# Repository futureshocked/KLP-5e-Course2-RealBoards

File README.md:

# KLP 5e — Course 2: Real Boards — project files

Companion project files for *KiCad Like a Pro, 5th Edition*, Course 2 ("Real boards"). Each
hands-on project is captured as a series of numbered stages, one per build step in the course,
so you can start from any point or check your own work against a known-good result.

Clone this repository, or download the stage folder you need, and carry on from there. Modules 1
and 2 work in the symbol and footprint editors with no project open, so their stages are library
folders; from Module 3 on, every stage is a complete KiCad project that opens on its own.

## About the course and the book series

To learn more about Course 2 and the *KiCad Like a Pro, 5th Edition* book series, visit the
[KLP 5e course page](https://techexplorations.com/kicad/course/).

## Projects

| Folder | Project | Used in |
|---|---|---|
| [`klp5e-c2-m1-drv8833-parts/`](klp5e-c2-m1-drv8833-parts/) | The DRV8833 symbol and footprint, authored from the datasheet, with Activities A1.1 and A2.1 | Modules 1 and 2 |
| [`klp5e-c2-m3-standin-board/`](klp5e-c2-m3-standin-board/) | The DRV8833 stand-in board, set up with net classes, sizes, custom rules and severities, with Activity A3.1; then routed and given its copper zones | Modules 3 and 4 |
| [`klp5e-c2-m5-led-matrix/`](klp5e-c2-m5-led-matrix/) | The four-cell MAX7219 LED matrix: one cell built, stamped four times and copied with Repeat Layout, with Activity A5.1 | Module 5 |
| [`klp5e-c2-m6-drv8833/`](klp5e-c2-m6-drv8833/) | The DRV8833 two-motor driver board, the capstone: sheet, board setup, driver stage placed first, routed, poured and finished with its silkscreen, with Activity A6.1; checked, plotted and ordered; then the recipes for its next revision; the bonus set 8U's sourcing fields and bills | Modules 6, 8U (bonus set), 9 and 11 |
| [`klp5e-c2-m7-drv8833-4motor/`](klp5e-c2-m7-drv8833-4motor/) | The capstone extended to four motors: the driver stage captured as a design block and placed a second time, with Activity A7.1; its sourcing fields, build variants and bills; plotted, with Activity A9.1 | Modules 7, 8 and 9 |
| [`module-10-assembly-handouts/`](module-10-assembly-handouts/) | The printable bench sheets for assembling the two-motor board with a stencil and hotplate, and by hand | Module 10 |

Each activity folder also holds the activity's slide deck, `slides.html`. Download it and open it in
a browser (press `F` for fullscreen, arrow keys to move), so you can keep the task on screen
instead of pausing the video.

More projects are added as each module is recorded. See each project's own README for what each
stage contains.

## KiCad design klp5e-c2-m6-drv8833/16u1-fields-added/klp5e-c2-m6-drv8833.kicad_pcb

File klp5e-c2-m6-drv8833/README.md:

# klp5e-c2-m6-drv8833 stages

One folder per step of Module 6's capstone: a two-motor driver board built round the DRV8833,
using the symbol and footprint you authored in Modules 1 and 2. The module draws the sheet, sets
the board up, places the driver stage first, routes the board and writes the rule that covers the chip's breakout,
pours the ground, labels the silkscreen and finishes it with the title block and logos. Each stage
is the project as it stood at the end of a lecture or bonus video and the start of the next one.

**Every stage is a complete KiCad project.** Open the `.kicad_pro` in a stage folder and it loads
on its own: the schematic, the board, the project's symbol and footprint library tables,
`Libraries/` (the DRV8833 symbol and footprint) and `datasheets/`. From `05-board-setup` on, the
stage also holds the `.kicad_dru` custom rules. Each stage also holds `tools/checknet.py`, the
netlist checker, and `tools/checkplacement.py`, the placement checker. Copy a stage folder out of
the repository before you work in it, and do not open two stages at once.

| Stage | State | Produced by |
|---|---|---|
| `00-start` | An empty A4 sheet with the title block, an empty board, the `Default` net class only, the DRV8833 library and datasheet, and the two checkers | bonus B6.1 |
| `01-classes-and-stage` | The `Power` and `Sense` net classes and their four patterns; the eight-part driver stage placed on the sheet, unannotated and unwired | lecture 6.4 |
| `02-sheet-placed` | Every part placed and annotated, with values and footprints filled in; still no wire | bonus B6.2 |
| `03-wired` | The sheet wired and labelled; ERC reports two `power_pin_not_driven` errors | lecture 6.5 |
| `04-netlist-clean` | Two `PWR_FLAG`s added; ERC clean; checknet's three checks pass | lecture 6.6 |
| `05-board-setup` | The fabricator's limits and mask clearance imported, default severities, two copper layers, the two-rule `.kicad_dru`; the board is still empty | lecture 6.7 |
| `06-outline` | Predefined track and via sizes, silkscreen default 0.15 mm, the 20 footprints on the board, the outline drawn | bonus B6.3 |
| `07-stage-placed` | The eight driver-stage parts placed; the other twelve still off the board | lecture 6.8 |
| `08-all-placed` | Every part at its table position, the driver stage locked; the board agrees with the sheet | bonus B6.4 |
| `09-bridge-a` | `VM_IN`, `VM`, `AOUT1`, `AOUT2` and `AISEN` routed on `F.Cu`. The start of A6.1 | lecture 6.9 |
| `10-bridge-b` | `J3` re-pinned and bridge B routed: `BOUT1`, `BOUT2` and `BISEN`. The worked solution to A6.1 | bonus B6.5 |
| `11-logic-routed` | The logic nets routed; only `GND` is left unconnected | bonus B6.6 |
| `12-breakout-area` | The rule area `U1_breakout` drawn round the chip, with a deliberate what-if: two narrow pieces on `AOUT1` and `BOUT1` that the DRC flags while the rule still follows the courtyard | lecture 6.10 |
| `13-rule-on-area` | The breakout rule aimed at the rule area; the DRC is clear | lecture 6.11 |
| `14-ground-poured` | The `GND` pour on both layers, with ties to the back for the ground pads in pockets of front copper. One tie via is still at the default size | lecture 6.12 |
| `15-labelled` | The designators and the connector legends on the silkscreen | lecture 6.13 |
| `16-finished` | The title block and the KiCad and Tech Explorations logos; the DRC reports no violation and parity is clean. The finished board, the start of Module 9 and of the bonus set 8U | bonus B6.7 |
| `16u1-fields-added` | The four sourcing field templates in the project; `U1`'s supplier fields corrected; `J1` to `J3`, `R2` and `R3` filled | bonus set, lecture 8.2U |
| `16u2-fields-filled` | `MPN`, `Manufacturer` and `Supplier` filled on all 13 lines of the bill | bonus set, B8.1U |
| `16u3-without-sense` | The design variant `without-sense`, with its overrides on `R2` and `R3` | bonus set, lecture 8.3U |
| `16u4-bills-exported` | The bill's export file set to `BOM/bom_${VARIANT}.csv`; `BOM/` holds one bill for each build | bonus set, lecture 8.5U |
| `16u5-assembly-bill` | The assembler's template columns and BOM names saved in the project; `BOM/` also holds the bill shaped to the template | bonus set, lecture 8.6U |
| `17-dfm-checked` | The same board after the DRC with the fab's numbers and the HQ DFM plugin; neither needed a fix | lecture 9.2 |
| `18-finish-enig` | The surface finish set to ENIG in Board Setup; nothing else changed | lecture 9.3 |
| `19-plotted` | The plot settings saved; `Gerber/` holds the nine Gerbers, the drill file and its map, the job file, the position file and `klp5e-c2-m6-drv8833-fab.zip`, the archive sent to the factory | lecture 9.4 |
| `20-fab-checked` | The same files after the three checks on the plotted files; nothing needed a fix. This is the board that was ordered and that Module 10 assembles, and the start of Module 11 | lecture 9.5 |
| `21-control-bus` | The four control lines drawn as the bus `CTRL{AIN1 AIN2 BIN1 BIN2}`; the board's control nets are now `/CTRL.AIN1` to `/CTRL.BIN2` | lecture 11.2 |
| `22-logic-table` | The DRV8833's H-bridge logic table on the back silkscreen | lecture 11.3 |
| `23-qr-code` | A QR code for `techexplorations.com/kicad`, made with the footprint wizard and saved as `te_qr_code` in `peters_custom_Library`, on the back silkscreen | lecture 11.4 |
| `24-teardrops` | Teardrops on the board's pads and vias; pours refilled | lecture 11.5 |

Stage `16-finished` adds a second project library, `Logo` (`Libraries/Logo.pretty`), holding the Tech
Explorations logo footprints. Its row is in the stage's `fp-lib-table`.

Stages `16u1` to `16u5` belong to the bonus set 8U, *The BOM and a second build*. It teaches
Module 8's skills again on this two-motor board: the sourcing fields, the `without-sense` build and
the bills. The stages branch off `16-finished`, and Module 9 does not continue from them.
`17-dfm-checked` follows `16-finished`, not `16u5-assembly-bill`, so the stages from `17` on have
no sourcing fields and no variants. Module 8 itself works on the four-motor board in
[`klp5e-c2-m7-drv8833-4motor/`](../klp5e-c2-m7-drv8833-4motor/).

Stages `17` to `20` are the board as it was checked and ordered in Module 9. Stages `21` to `24`
are the recipes of Module 11: touches for the board's next revision, so they hold no plotted files
and nothing in them was ordered.

## Checking the netlist (lecture 6.6)

From a stage folder, from `03-wired` on:

```bash
kicad-cli sch export netlist -o net.net klp5e-c2-m6-drv8833.kicad_sch
python3 tools/checknet.py net.net --nets
python3 tools/checknet.py net.net --u1-pins
python3 tools/checknet.py net.net --classes
```

On `04-netlist-clean` and later, all three pass.

## Checking the placement (bonus B6.4)

From a stage folder, from `08-all-placed` on:

```bash
python3 tools/checkplacement.py --outline --fit --overlap --proximity
```

On `07-stage-placed` it fails, because twelve parts are still off the board.

## Activity A6.1

[`A6.1-activity/`](A6.1-activity/) has everything for the activity in its own README: where you
start, the task, the settings, the acceptance list and what to do if you get stuck. The folder also
holds a record sheet (`record-sheet.md`) and the lecture's slide deck (`slides.html`). Start from
`09-bridge-a`. The worked solution is bonus B6.5, and its stage is `10-bridge-b`.

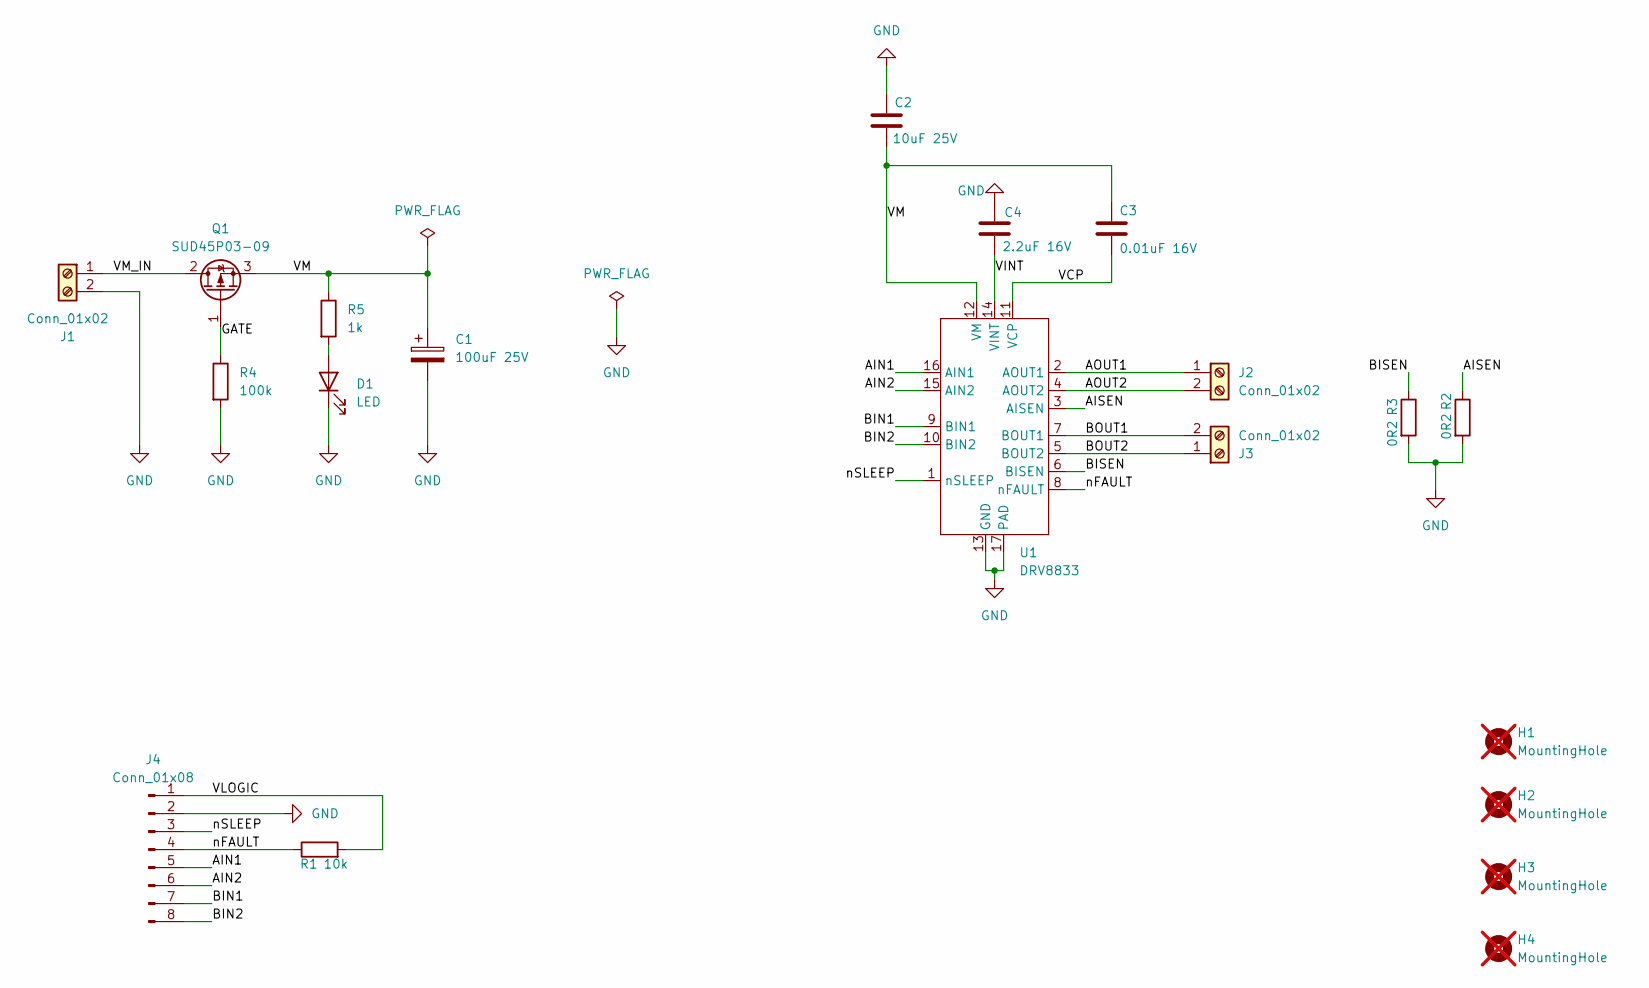
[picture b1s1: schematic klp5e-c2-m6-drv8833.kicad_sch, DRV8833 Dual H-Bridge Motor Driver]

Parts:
C1: 100uF 25V; CP_Radial_D6.3mm_P2.50mm
C2: 10uF 25V; C_0805_2012Metric
C3: 0.01uF 16V; C_0603_1608Metric
C4: 2.2uF 16V; C_0603_1608Metric
D1: LED; LED_0805_2012Metric
H1, H2, H3, H4: MountingHole; MountingHole_3.2mm_M3; not fitted
J1, J2, J3: Conn_01x02; TerminalBlock_Phoenix_MKDS-1,5-2-5.08_1x02_P5.08mm_Horizont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; MPN 1715721
J4: Conn_01x08; PinHeader_1x08_P2.54mm_Vertical
Q1: SUD45P03-09; TO-252-2
R1: 10k; R_0603_1608Metric
R2, R3: 0R2; R_1206_3216Metric; MPN CSR1206FKR200
R4: 100k; R_0603_1608Metric
R5: 1k; R_0603_1608Metric
U1: DRV8833; HTSSOP-16-1EP_DRV8833_PD; MPN DRV8833PWPR

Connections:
/AIN1: J4.5, U1.16 (AIN1)
/AIN2: J4.6, U1.15 (AIN2)
/AISEN: R2.1, U1.3 (AISEN)
/AOUT1: J2.1, U1.2 (AOUT1)
/AOUT2: J2.2, U1.4 (AOUT2)
/BIN1: J4.7, U1.9 (BIN1)
/BIN2: J4.8, U1.10 (BIN2)
/BISEN: R3.1, U1.6 (BISEN)
/BOUT1: J3.2, U1.7 (BOUT1)
/BOUT2: J3.1, U1.5 (BOUT2)
/GATE: Q1.1 (G), R4.1
/VCP: C3.2, U1.11 (VCP)
/VINT: C4.2, U1.14 (VINT)
/VLOGIC: J4.1, R1.2
/VM: C1.1, C2.2, C3.1, Q1.3 (S), R5.1, U1.12 (VM)
/VM_IN: J1.1, Q1.2 (D)
/nFAULT: J4.4, R1.1, U1.8 (nFAULT)
/nSLEEP: J4.3, U1.1 (nSLEEP)
GND: C1.2, C2.1, C4.1, D1.1 (K), J1.2, J4.2, R2.2, R3.2, R4.2, U1.13 (GND), U1.17 (PAD)
unnamed: D1.2 (A), R5.2

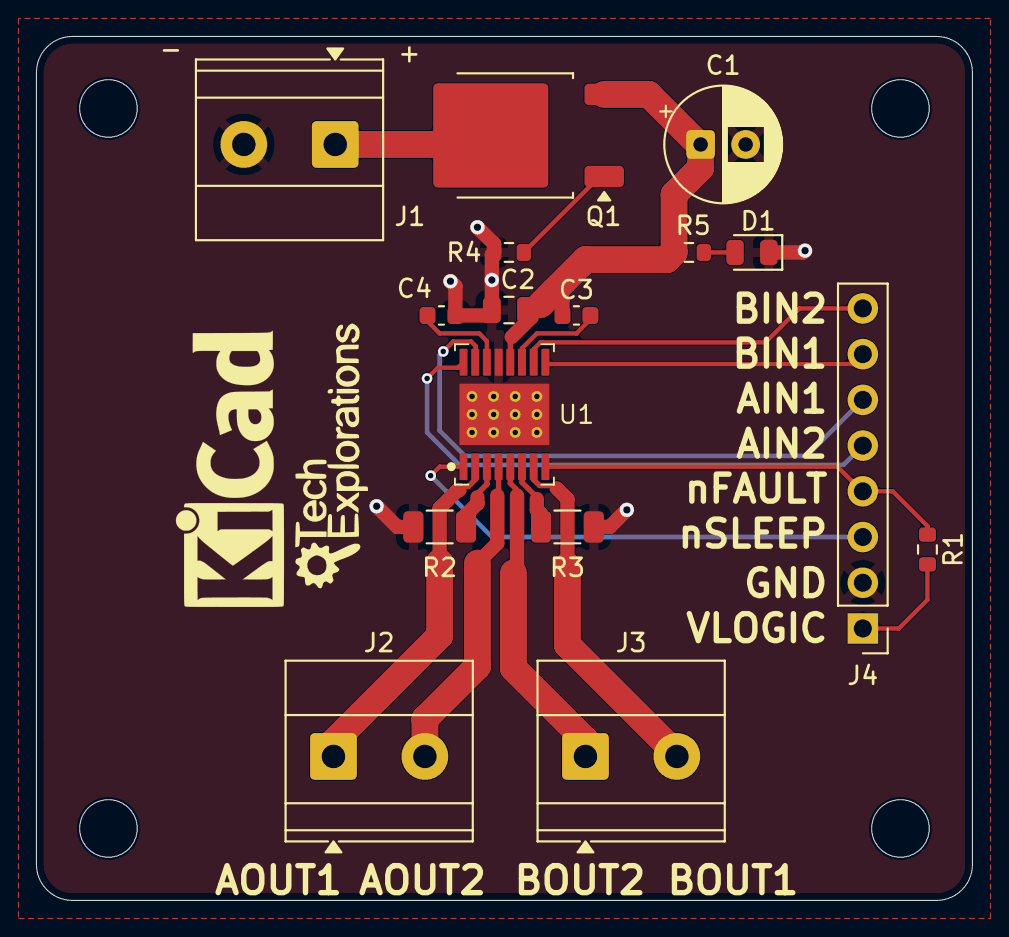
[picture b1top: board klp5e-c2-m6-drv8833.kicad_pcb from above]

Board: 2 copper layers, 52.0 x 48.0 mm, 20 parts (0 on the bottom side), 20 nets.

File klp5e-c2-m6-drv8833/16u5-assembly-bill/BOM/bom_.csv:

"Reference","Value","Footprint","Qty","DNP","SupplierURL","MPN","Manufacturer","Supplier"
"C1","100uF 25V","Capacitor_THT:CP_Radial_D6.3mm_P2.50mm","1","","","EEU-FR1E101","Panasonic","Farnell UK"
"C2","10uF 25V","Capacitor_SMD:C_0805_2012Metric","1","","","GRM21BR61E106KA73L","Murata","TTI Europe"
"C3","0.01uF 16V","Capacitor_SMD:C_0603_1608Metric","1","","","0603YC103JAT2A","KYOCERA AVX","Future Electronics EMEA"
"C4","2.2uF 16V","Capacitor_SMD:C_0603_1608Metric","1","","","EMK107BB7225KA-T","Taiyo Yuden","RS UK"
"D1","LED","LED_SMD:LED_0805_2012Metric","1","","","150080GS75000","Würth Elektronik","Farnell UK"
"J1,J2,J3","Conn_01x02","TerminalBlock_Phoenix:TerminalBlock_Phoenix_MKDS-1,5-2-5.08_1x02_P5.08mm_Horizontal","3","","","1715721","Phoenix Contact","Farnell UK"
"J4","Conn_01x08","Connector_PinHeader_2.54mm:PinHeader_1x08_P2.54mm_Vertical","1","","","61300811121","Würth Elektronik","DigiKey"
"Q1","SUD45P03-09","Package_TO_SOT_SMD:TO-252-2","1","","","SUD45P03-09-GE3","Vishay","Farnell UK"
"R1","10k","Resistor_SMD:R_0603_1608Metric","1","","","RC0603FR-0710KL","Yageo","RS UK"
"R2,R3","0R2","Resistor_SMD:R_1206_3216Metric","2","","","CSR1206FKR200","Stackpole Electronics","Future Electronics NA"
"R4","100k","Resistor_SMD:R_0603_1608Metric","1","","","RC0603FR-07100KL","Yageo","RS UK"
"R5","1k","Resistor_SMD:R_0603_1608Metric","1","","","RC0603FR-071KL","Yageo","Farnell UK"
"U1","DRV8833","peters_custom_Library:HTSSOP-16-1EP_DRV8833_PD","1","","https://uk.farnell.com/texas-instruments/drv8833pwpr/ic-moto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","DRV8833PWPR","Texas Instruments","Farnell UK"

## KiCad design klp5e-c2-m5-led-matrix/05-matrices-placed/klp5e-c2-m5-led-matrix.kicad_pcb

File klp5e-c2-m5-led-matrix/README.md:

# klp5e-c2-m5-led-matrix stages

One folder per step of Module 5's warm-up board: four MAX7219 cells, each driving an 8 × 8 LED
matrix, on a 100 × 50 mm board, fed by an Arduino Nano. The module builds one cell, stamps it four
times in the schematic, and routes it once on the board before copying it to the other three. Each
stage is the project as it stood at the end of a lecture and the start of the next one.

**Every stage is a complete KiCad project.** Open the `.kicad_pro` in a stage folder and it loads
on its own: the schematic, the board, the `.kicad_dru` custom rules, the project's symbol,
footprint and design block library tables, and `Libraries/`, which holds the matrix, the Nano and
the logo footprints, the symbols, the `MAX7219-Cell` design block and the 3D models. Each stage
also holds `tools/checknet.py`, the netlist checker used in lecture 5.5. Copy a stage folder out of
the repository before you work in it, and do not open two stages at once.

| Stage | State | Produced by |
|---|---|---|
| `00-start` | The once-only parts (the Nano, USB-C input, the MOSFET power switch, the buttons and their resistors), power symbols and labels; no cell yet; the board outline and the fabricator's limits; no footprints on the board | bonus B5.1 |
| `01-first-cell` | The `POWER` net class; cell 1 drawn and wired, `DIN` and `DOUT` bare | lecture 5.3 |
| `02-cell-footprints` | The cell's five footprints assigned | bonus B5.2 |
| `03-four-cells` | The cell saved as the `MAX7219-Cell` design block and placed three more times; the cascade links drawn, **with one mislabelled link**: the mistake lecture 5.5 finds | lecture 5.4 |
| `04-netlist-clean` | The link label fixed; ERC clean; all five checknet runs pass | lecture 5.5 |
| `05-matrices-placed` | Footprints on the board as four groups; matrices `DS1` to `DS4` at 20 mm pitch, locked | lecture 5.6 |
| `06-once-only-placed` | The once-only parts and the four mounting holes placed; cells 2 to 4 roughly under their matrices | bonus B5.3 |
| `07-reference-started` | Cell 1 routed on the back | lecture 5.7 |
| `08-reference-routed` | The same board as `07`: cell 1, the reference cell, fully routed | lecture 5.7 |
| `09-repeated` | Groups renamed `DS1` to `DS4`, each with a placement rule area; cells 2 to 4 placed and routed from cell 1 by Repeat Layout | lecture 5.8 |
| `10-shared-wiring` | The wiring the cells share (power, clock, load and the cascade) drawn into and out of cells 1 and 2. The start of A5.1 | bonus B5.5 |
| `11-copied` | Cells 3 and 4 given their shared wiring by one Repeat Layout from cell 2, unrepaired. A5.1's worked solution | bonus B5.6 |
| `12-repaired` | The two stacked vias the copy left at the cell 3 and cell 4 seams removed; no DRC warnings, only `GND` unconnected | lecture 5.9 |
| `13-first-pour` | One `GND` zone on both layers, filled: much of the back's copper is cut away between the cells' tracks | lecture 5.10 |
| `14-stitched` | `DIN1` and the cascade links re-routed; `GND` vias stitched through the pour until every filled piece reaches one; nothing unconnected | bonus B5.7 |
| `15-finished` | Reference designators resized, the silkscreen labels and the board's name and version added, the Nano's 3D model placed: the finished board | bonus B5.8 |

Up to `12-repaired`, every stage leaves `GND` unconnected: the copper pour joins it in lecture
5.10, and the stitching vias in `14-stitched` finish the job. When you open `13-first-pour` or a
later stage, press B to refill the pour before you read it or run the DRC.

## Checking the netlist (lecture 5.5)

From a stage folder, from `03-four-cells` on:

```bash
kicad-cli sch export netlist -o net.net klp5e-c2-m5-led-matrix.kicad_sch
for n in 1 2 3 4; do python3 tools/checknet.py net.net --cell $n; done
python3 tools/checknet.py net.net --cascade 4
```

On `03-four-cells` the cascade run fails at the mislabelled link; on `04-netlist-clean` all five
runs pass.

## Activity A5.1

[`A5.1-activity/`](A5.1-activity/) has everything for the activity in its own README: where you
start, the steps, the acceptance list and where you finish. The folder also holds a record sheet
(`record-sheet.md`) and the lecture's slide deck (`slides.html`). Start from `10-shared-wiring`,
and compare your result with `11-copied` only after you have checked every line of the acceptance
list.

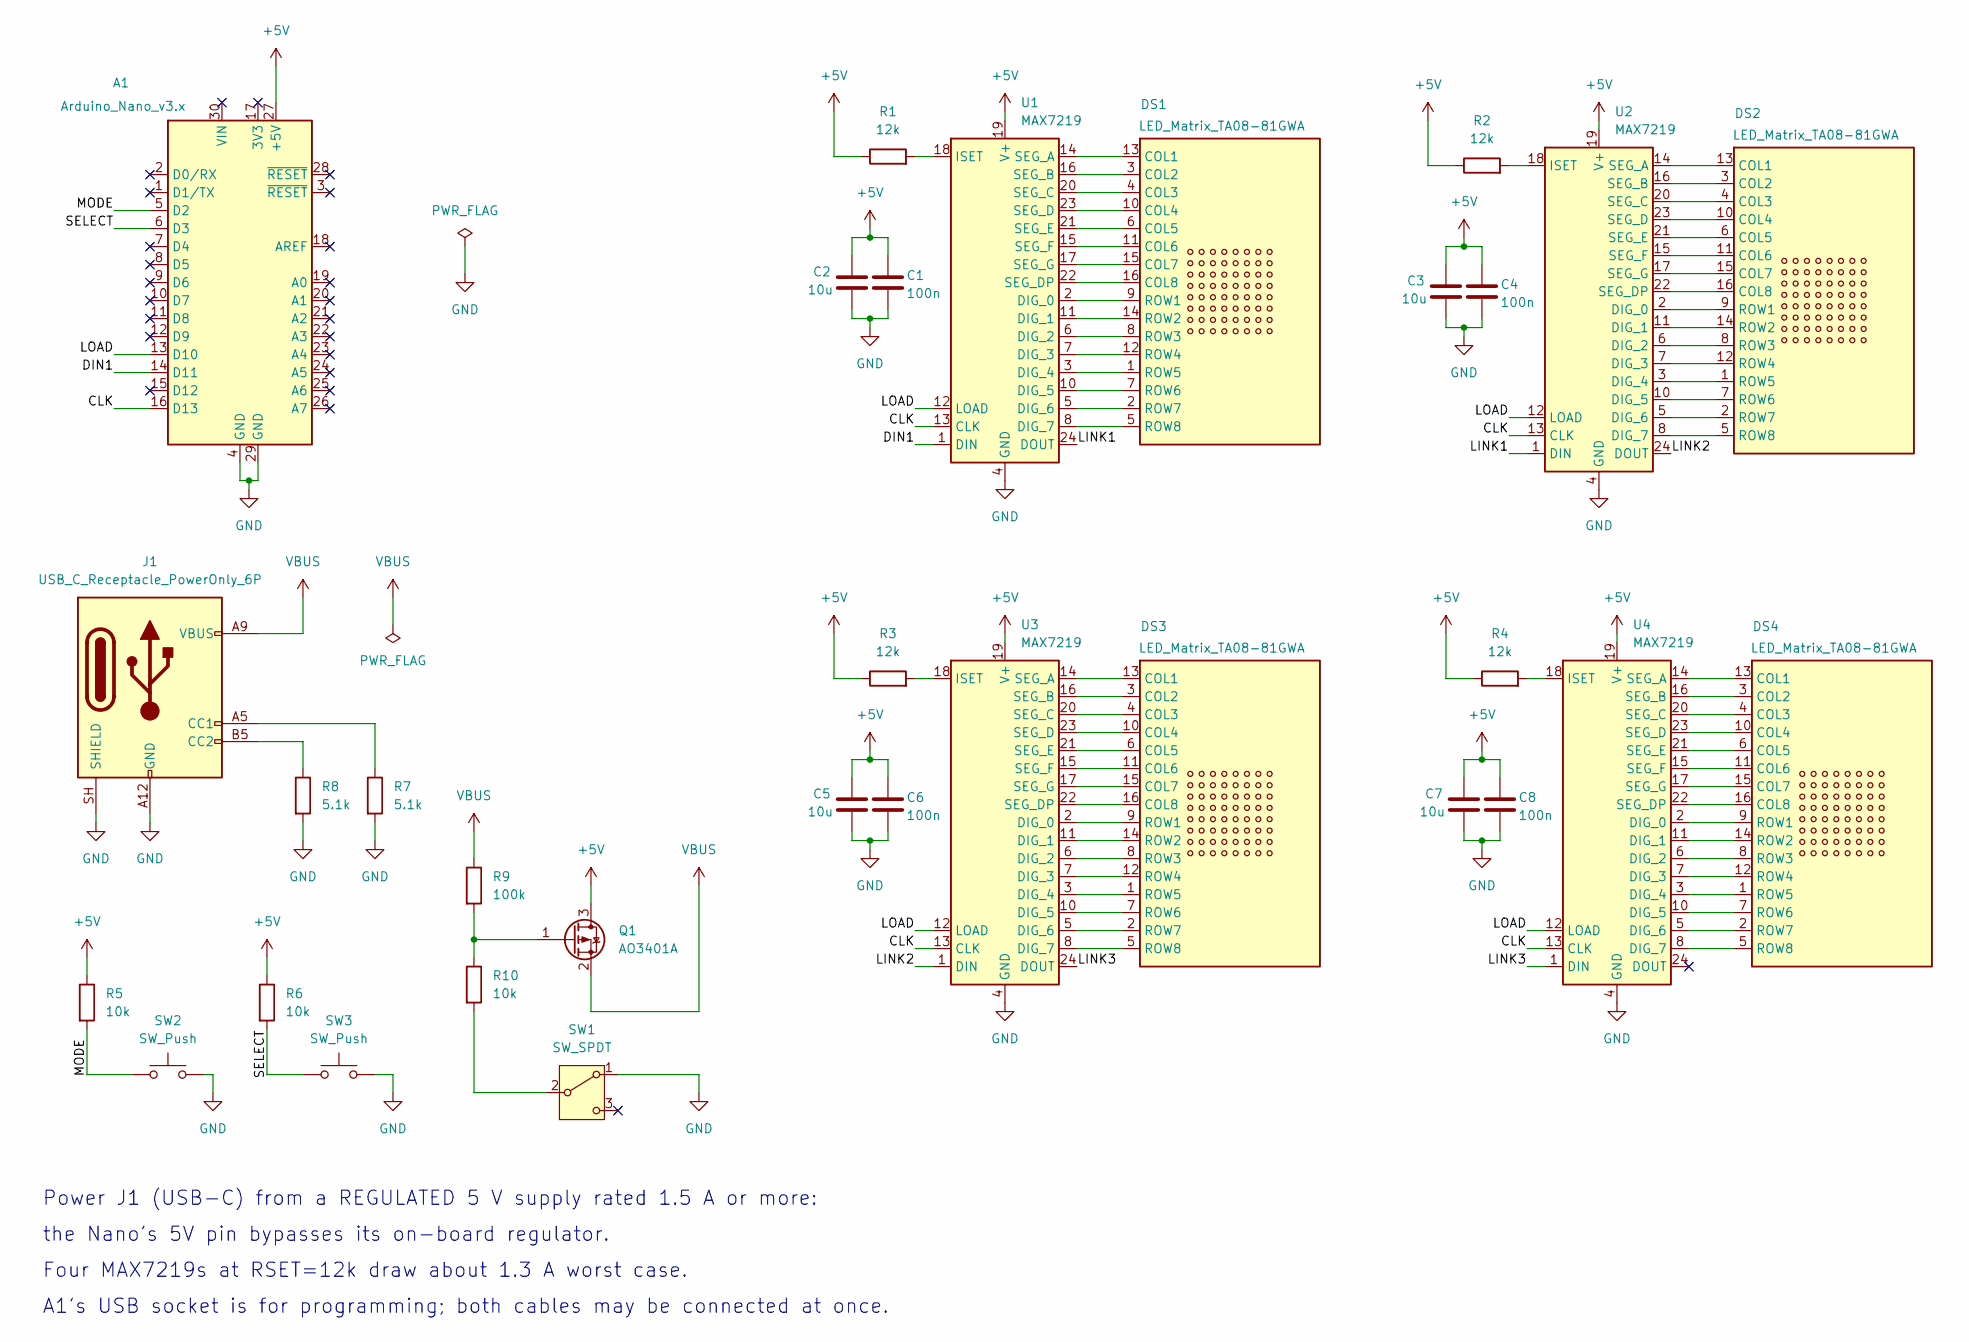
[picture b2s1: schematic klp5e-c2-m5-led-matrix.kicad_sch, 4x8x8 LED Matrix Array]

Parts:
A1: Arduino_Nano_v3.x; Arduino_Nano
C1, C4, C6, C8: 100n; C_0603_1608Metric
C2, C3, C5, C7: 10u; C_0805_2012Metric
DS1, DS2, DS3, DS4: LED_Matrix_TA08-81GWA; LED_Matrix_TA08-81_20mm_8x8
J1: USB_C_Receptacle_PowerOnly_6P; USB_C_Receptacle_GCT_USB4125-xx-x-0190_6P_TopMnt_Horizontal
Q1: AO3401A; SOT-23
R1, R2, R3, R4: 12k; R_0603_1608Metric
R5, R6, R10: 10k; R_0603_1608Metric
R7, R8: 5.1k; R_0603_1608Metric
R9: 100k; R_0603_1608Metric
SW1: SW_SPDT; SW_CK_JS202011AQN_DPDT_Angled
SW2, SW3: SW_Push; SW_PUSH_6mm
U1, U2, U3, U4: MAX7219; SOIC-24W_7.5x15.4mm_P1.27mm

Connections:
+5V: A1.27 (+5V), C1.1, C2.1, C3.1, C4.1, C5.1, C6.1, C7.1, C8.1, Q1.3 (D), R1.1, R2.1, R3.1, R4.1, R5.1, R6.1, U1.19 (V+), U2.19 (V+), U3.19 (V+), U4.19 (V+)
/CLK: A1.16 (D13), U1.13 (CLK), U2.13 (CLK), U3.13 (CLK), U4.13 (CLK)
/DIN1: A1.14 (D11), U1.1 (DIN)
/LINK1: U1.24 (DOUT), U2.1 (DIN)
/LINK2: U2.24 (DOUT), U3.1 (DIN)
/LINK3: U3.24 (DOUT), U4.1 (DIN)
/LOAD: A1.13 (D10), U1.12 (LOAD), U2.12 (LOAD), U3.12 (LOAD), U4.12 (LOAD)
/MODE: A1.5 (D2), R5.2, SW2.1
/SELECT: A1.6 (D3), R6.2, SW3.1
GND: A1.4 (GND), A1.29 (GND), C1.2, C2.2, C3.2, C4.2, C5.2, C6.2, C7.2, C8.2, J1.A12 (GND), J1.B12 (GND), J1.SH (SHIELD), R7.2, R8.2, SW1.1 (A), SW2.2, SW3.2, U1.4 (GND), U1.9 (GND), U2.4 (GND), U2.9 (GND), U3.4 (GND), U3.9 (GND), U4.4 (GND), U4.9 (GND)
unnamed: DS1.13 (COL1), U1.14 (SEG_A)
unnamed: DS1.3 (COL2), U1.16 (SEG_B)
unnamed: DS1.4 (COL3), U1.20 (SEG_C)
unnamed: DS1.10 (COL4), U1.23 (SEG_D)
unnamed: DS1.6 (COL5), U1.21 (SEG_E)
unnamed: DS1.11 (COL6), U1.15 (SEG_F)
unnamed: DS1.15 (COL7), U1.17 (SEG_G)
unnamed: DS1.16 (COL8), U1.22 (SEG_DP)
unnamed: DS1.9 (ROW1), U1.2 (DIG_0)
unnamed: DS1.14 (ROW2), U1.11 (DIG_1)
unnamed: DS1.8 (ROW3), U1.6 (DIG_2)
unnamed: DS1.12 (ROW4), U1.7 (DIG_3)
unnamed: DS1.1 (ROW5), U1.3 (DIG_4)
unnamed: DS1.7 (ROW6), U1.10 (DIG_5)
unnamed: DS1.2 (ROW7), U1.5 (DIG_6)
unnamed: DS1.5 (ROW8), U1.8 (DIG_7)
unnamed: DS2.13 (COL1), U2.14 (SEG_A)
unnamed: DS2.3 (COL2), U2.16 (SEG_B)
unnamed: DS2.4 (COL3), U2.20 (SEG_C)
unnamed: DS2.10 (COL4), U2.23 (SEG_D)
unnamed: DS2.6 (COL5), U2.21 (SEG_E)
unnamed: DS2.11 (COL6), U2.15 (SEG_F)
unnamed: DS2.15 (COL7), U2.17 (SEG_G)
unnamed: DS2.16 (COL8), U2.22 (SEG_DP)
unnamed: DS2.9 (ROW1), U2.2 (DIG_0)
unnamed: DS2.14 (ROW2), U2.11 (DIG_1)
unnamed: DS2.8 (ROW3), U2.6 (DIG_2)
unnamed: DS2.12 (ROW4), U2.7 (DIG_3)
unnamed: DS2.1 (ROW5), U2.3 (DIG_4)
unnamed: DS2.7 (ROW6), U2.10 (DIG_5)
unnamed: DS2.2 (ROW7), U2.5 (DIG_6)
unnamed: DS2.5 (ROW8), U2.8 (DIG_7)
unnamed: DS3.13 (COL1), U3.14 (SEG_A)
unnamed: DS3.3 (COL2), U3.16 (SEG_B)
unnamed: DS3.4 (COL3), U3.20 (SEG_C)
unnamed: DS3.10 (COL4), U3.23 (SEG_D)
unnamed: DS3.6 (COL5), U3.21 (SEG_E)
unnamed: DS3.11 (COL6), U3.15 (SEG_F)
unnamed: DS3.15 (COL7), U3.17 (SEG_G)
unnamed: DS3.16 (COL8), U3.22 (SEG_DP)
unnamed: DS3.9 (ROW1), U3.2 (DIG_0)
unnamed: DS3.14 (ROW2), U3.11 (DIG_1)
unnamed: DS3.8 (ROW3), U3.6 (DIG_2)
unnamed: DS3.12 (ROW4), U3.7 (DIG_3)
unnamed: DS3.1 (ROW5), U3.3 (DIG_4)
unnamed: DS3.7 (ROW6), U3.10 (DIG_5)
unnamed: DS3.2 (ROW7), U3.5 (DIG_6)
unnamed: DS3.5 (ROW8), U3.8 (DIG_7)
unnamed: DS4.13 (COL1), U4.14 (SEG_A)
unnamed: DS4.3 (COL2), U4.16 (SEG_B)
unnamed: DS4.4 (COL3), U4.20 (SEG_C)
unnamed: DS4.10 (COL4), U4.23 (SEG_D)
unnamed: DS4.6 (COL5), U4.21 (SEG_E)
unnamed: DS4.11 (COL6), U4.15 (SEG_F)
unnamed: DS4.15 (COL7), U4.17 (SEG_G)
unnamed: DS4.16 (COL8), U4.22 (SEG_DP)
unnamed: DS4.9 (ROW1), U4.2 (DIG_0)
unnamed: DS4.14 (ROW2), U4.11 (DIG_1)
unnamed: DS4.8 (ROW3), U4.6 (DIG_2)
unnamed: DS4.12 (ROW4), U4.7 (DIG_3)
unnamed: DS4.1 (ROW5), U4.3 (DIG_4)
unnamed: DS4.7 (ROW6), U4.10 (DIG_5)
unnamed: DS4.2 (ROW7), U4.5 (DIG_6)
unnamed: DS4.5 (ROW8), U4.8 (DIG_7)
unnamed: J1.A5 (CC1), R7.1
unnamed: J1.B5 (CC2), R8.1
unnamed: Q1.1 (G), R9.2, R10.1
unnamed: R10.2, SW1.2 (B)
unnamed: R1.2, U1.18 (ISET)
unnamed: R2.2, U2.18 (ISET)
unnamed: R3.2, U3.18 (ISET)
unnamed: R4.2, U4.18 (ISET)
VBUS: J1.A9 (VBUS), J1.B9 (VBUS), Q1.2 (S), R9.1

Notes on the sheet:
Four MAX7219s at RSET=12k draw about 1.3 A worst case.
Power J1 (USB-C) from a REGULATED 5 V supply rated 1.5 A or more:
the Nano's 5V pin bypasses its on-board regulator.
A1's USB socket is for programming; both cables may be connected at once.

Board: 2 copper layers, 32 parts (0 on the bottom side), 83 nets, no tracks yet.

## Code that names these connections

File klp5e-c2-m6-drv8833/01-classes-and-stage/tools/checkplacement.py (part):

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    "U1": ("peters_custom_Library:HTSSOP-16-1EP_DRV8833_PD", 0.00, 0.00, 90),
    # C2, C3 and C4 shifted slightly and C2 turned 180 deg during power routing, so that
    # VM arrives on the pad nearest the trunk instead of crossing the part to reach it.
    "C3": ("Capacitor_SMD:C_0603_1608Metric", +4.00, +5.50, 0),      # VCP, pin 11, right
    "C2": ("Capacitor_SMD:C_0805_2012Metric", +0.25, +5.80, 180),    # VM,  pin 12
    "C4": ("Capacitor_SMD:C_0603_1608Metric", -3.50, +5.50, 0),      # VINT, pin 14, left
    # R2 is turned 180 deg so its AISEN pad faces U1 rather than pointing away from it.
    # Both dropped 0.75 mm during the channel A and B redraw, because six current-carrying
    # nets escape U1's bottom row at 0.65 mm pitch and the fanout needs the room. That put
    # them 4.26 and 4.20 mm from their sense pins instead of 3.62; see PROXIMITY below.
    "R2": ("Resistor_SMD:R_1206_3216Metric", -3.60, -6.25, 180),     # AISEN, pin 3, left
    "R3": ("Resistor_SMD:R_1206_3216Metric", +3.50, -6.25, 0),       # BISEN, pin 6, right
    "J2": ("TerminalBlock_Phoenix:TerminalBlock_Phoenix_MKDS-1,5-2-5.08_1x02_P5.08mm_Horizontal", -9.50, -19.00, 0),   # motor A, left
    "J3": ("TerminalBlock_Phoenix:TerminalBlock_Phoenix_MKDS-1,5-2-5.08_1x02_P5.08mm_Horizontal", +4.50, -19.00, 0),   # motor B, right
}
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

# U1 pin groups, to prove the chip is the right way up rather than assume it
SUPPLY_PINS = {"11": "VCP", "12": "VM", "13": "GND", "14": "VINT"}
MOTOR_PINS = {"2": "AOUT1", "3": "AISEN", "4": "AOUT2", "5": "BOUT2", "6": "BISEN", "7": "BOUT1"}


def check_orientation(place, height):
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
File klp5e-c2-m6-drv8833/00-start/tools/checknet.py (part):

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"""Read a KiCad netlist and assert what Module 6 draws on the capstone's sheet.

Course 2's copy of Volume 2's tools/checknet.py (M6 P2, 2026-10-28). One change: J3's two
pins may be in either order, as a pair. Module 6 wires J3 as the sheet reads (BOUT1 on pin 1,
L6.5) and re-pins it while routing bridge B (A6.1, worked in bonus B6.5); the book's checker
knows only the re-pinned order. Everything else is the book's, unchanged.

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# there is simply nothing of them to assert here.
# ---------------------------------------------------------------------------
NETS = {
    "/VM_IN":  {("J1", "1"), ("Q1", "2")},                       # Q1 pin 2 = D
    "/VM":     {("Q1", "3"), ("C1", "1"), ("C2", "1"), ("C3", "1"),
                ("R5", "1"), ("U1", "12")},                      # Q1 pin 3 = S
    "GND":     {("J1", "2"), ("C1", "2"), ("C2", "2"), ("C4", "2"), ("R4", "2"),
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    "/AIN2":   {("U1", "15"), ("J4", "6")},
    "/BIN1":   {("U1", "9"), ("J4", "7")},
    "/BIN2":   {("U1", "10"), ("J4", "8")},
    "/GATE":   {("Q1", "1"), ("R4", "1")},                       # Q1 pin 1 = G
}

# J3 after the re-pin: both of bridge B's outputs change pins together.
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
